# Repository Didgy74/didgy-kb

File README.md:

# didgy-kb
A catch-all repo for any keyboards I design.

These designs are all designed with [Ergogen](https://github.com/ergogen/ergogen).

# Mitten

This design has the following properties:
 - 30 keys
 - Split
 - Columnar stagger
 - Column splay on the outer columns
 - Wireless
 - Reversible PCB
 - (Very) Low profile (Choc Mini)
 - Choc spacing in Y direction
 - MX spacing in X direction
 - 1u keys for fingers
 - 1.5u keys for thumbs
 - Includes mountplate
 - Standard ProMicro support (Note that it's wireless only, so use a compatible MCU with Bluetooth connectivity)

In short, this design is heavily inspired by the [Ferris](https://github.com/pierrechevalier83/ferris) (or more specifically, the [Sweep](https://github.com/davidphilipbarr/Sweep)). This keyboard is very similar with a few key design differences:
 - Stagger adjusted for hands that have a short index finger
 - Outer columns are splayed
 - Removed one key from innermost column and outermost column.
 - Choc Mini support
 - Larger thumbkeys (1.5u)
 - Designed for wireless operation **only**
 - Includes mountplate

### Information

**Main PCB thickness:** 1.6mm

**Mount plate thickness:** 1.6mm

Mount plate is mostly for making the design sturdier and holding keys in place a bit better.

**Connector:** Molex PicoBlade 2-pin horizontal (Often mislabeled as Micro JST in stores)

**Key switches:** Kailh Choc Mini PG1232 (https://www.aliexpress.com/item/4000277394324.html)

Personal note: Try using 35g springs with linear (black) motion.

**MCU sockets:** Mill-Max Interconnect Machined Pin Socket. Pitch 2.54mm. Height above PCB: 7mm.
Part no. 801-XX-XXX-10-001000. You need at least 12 pins wide, any more can be broken off.

**Underside material:** Neoprene (need actual testing still)

**Keycaps:** MBK profile Choc (https://splitkb.com/collections/switches-and-keycaps/products/blank-mbk-choc-low-profile-keycaps)

**Power switch:** 7-pin micro SPDT

**MCU:** nice!nano

Xiao Seeed was considered for its smaller size, but since battery is mounted under the MCU, the battery would have to become too small anyways.

**MCU socket pins:** Mill-Max gold pins. Part no. 3320-0-00-15-00-00-03-0. (https://splitkb.com/collections/keyboard-parts/products/mill-max-low-profile-sockets?variant=32170972020813)

These could be thicker / longer, fit is not very good.

### Instructions

The MCU has to be mounted **face down** by default.

By default, all jumpers need to be shorted on the **opposite side** of where components are mounted.

### Future design work
I intend to keep iterating on this design over time, here are a few ideas I would like to eventually realize:
 - Add wired connectivity (but only if I, or a number of users request it)
 - Remove a key from the pinky column
 - **Possiby** try out a very low profile rotary encoder
 - Tighter vertical keyspacing (would require custom keycap work)
 - Choc Mini support
 - Add instructions for automatically routing the PCB

Other than that, I'll probably make adjustments to the stagger and key placement over time.

### Configuration 

While this is currently configured to fit my hands specifically, I am very much interested in creating a very parametric design. I try to keep the .yaml file commented enough to easily understand how to modify it. For instance, you could easily switch to using MX spacing by modifying the lines
```yaml
  keyspacingx: cx
  keyspacingy: cy
```
to
```yaml
  keyspacingx: u
  keyspacingy: u
```
and even switch to MX switch footprints by finding the YAML variable named `key_footprints`. Other configurable values currently include margin around key switches, rotation of the home thumbkey. I plan to add more of configuration in the future.

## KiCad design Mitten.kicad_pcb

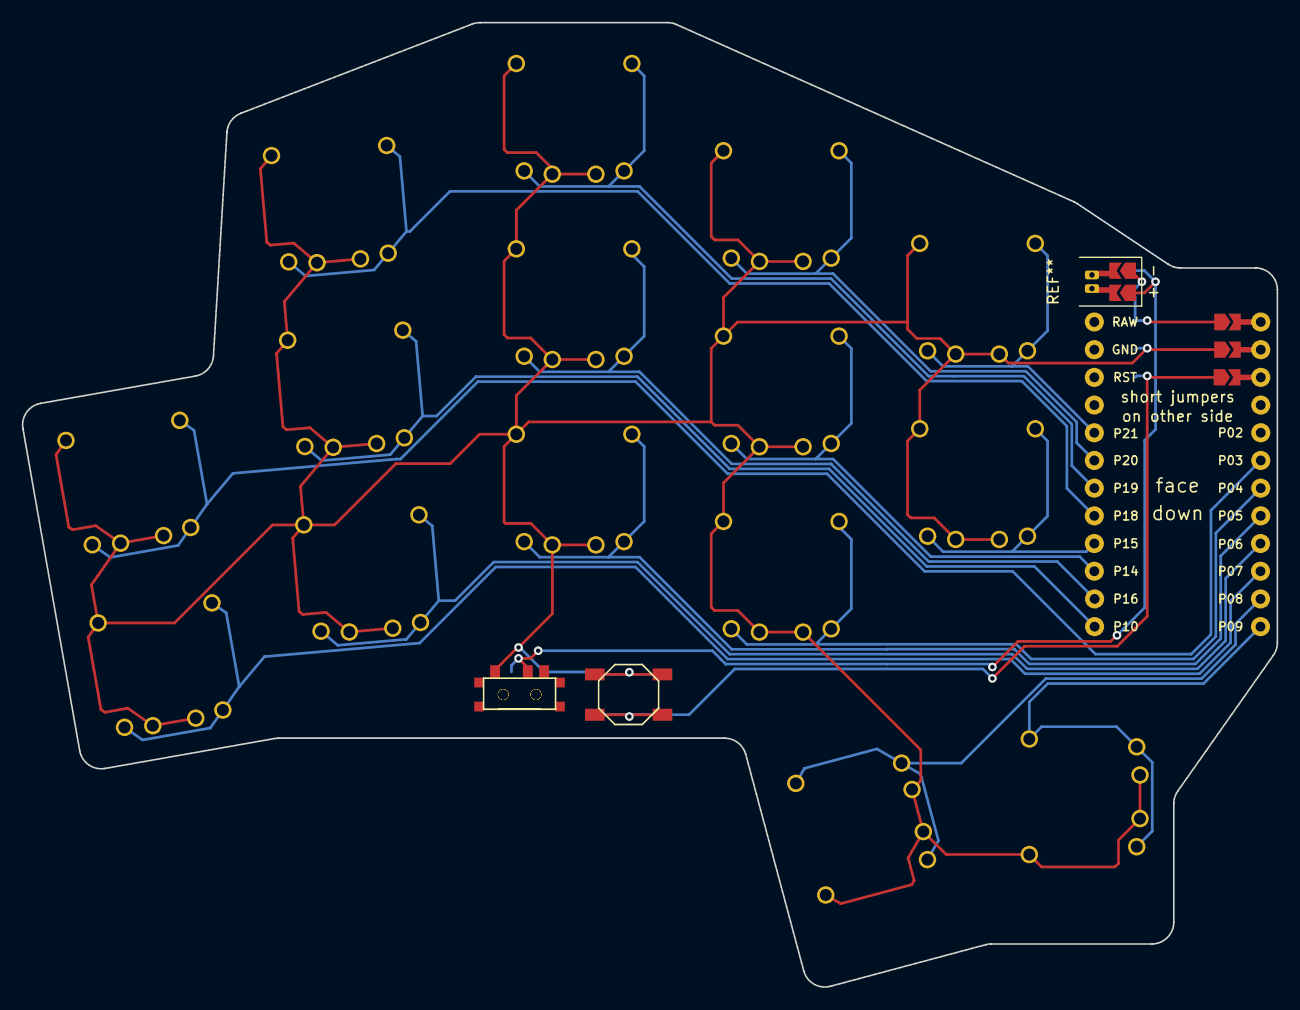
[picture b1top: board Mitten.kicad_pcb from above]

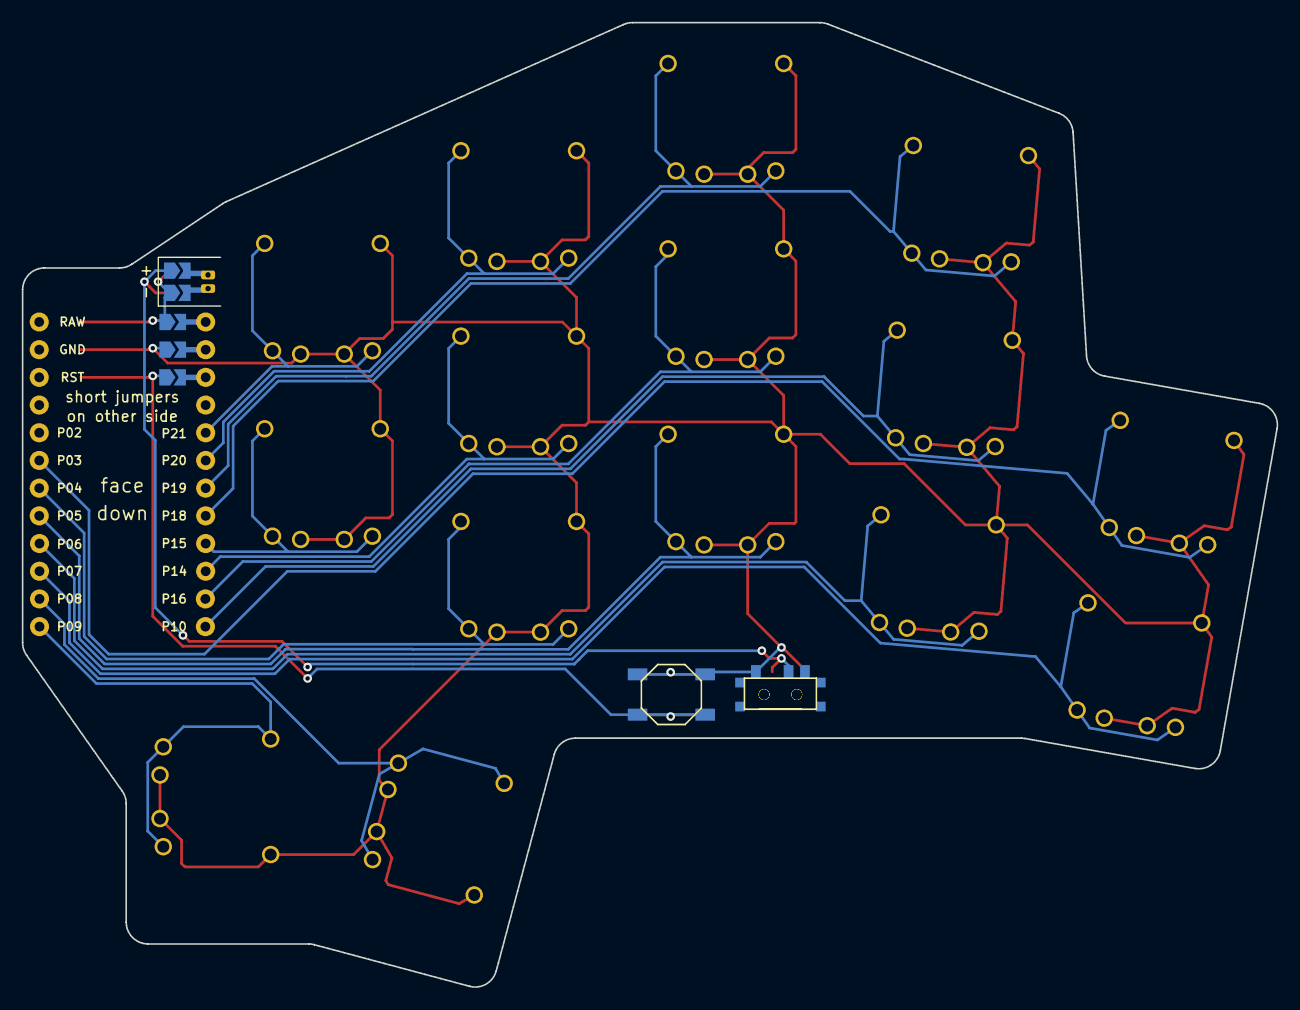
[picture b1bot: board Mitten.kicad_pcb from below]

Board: 2 copper layers, 115.1 x 88.5 mm, 20 parts (2 on the bottom side), 18 nets.

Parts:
B1, B1#2: SW_TACT_ALPS_SKQGABE010
MCU1: ProMicroReversible
S1, S2, S3, S4, S5, S6, S7, S8, S9, S10, S11, S12, S13, S14, S15: Choc Mini
T1, T1#2: SPDT_C128955

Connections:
Bminus: T1.2, T1#2.2
GND: B1.2, B1#2.2, MCU1.2, S1.2, S2.2, S3.2, S4.2, S5.2, S6.2, S7.2, S8.2, S9.2, S10.2, S11.2, S12.2, S13.2, S14.2, S15.2, T1.1, T1#2.1
RST: B1.1, B1#2.1, MCU1.3
home_default: MCU1.24, S14.1
index_bottom: MCU1.19, S9.1
index_home: MCU1.10, S10.1
index_topmost: MCU1.6, S11.1
innermost_bottom: MCU1.9, S12.1
innermost_topmost: MCU1.5, S13.1
middle_bottom: MCU1.20, S6.1
middle_home: MCU1.11, S7.1
middle_topmost: MCU1.7, S8.1
near_default: MCU1.23, S15.1
pinky_bottom: MCU1.22, S1.1
pinky_home: MCU1.18, S2.1
ring_bottom: MCU1.21, S3.1
ring_home: MCU1.12, S4.1
ring_topmost: MCU1.8, S5.1

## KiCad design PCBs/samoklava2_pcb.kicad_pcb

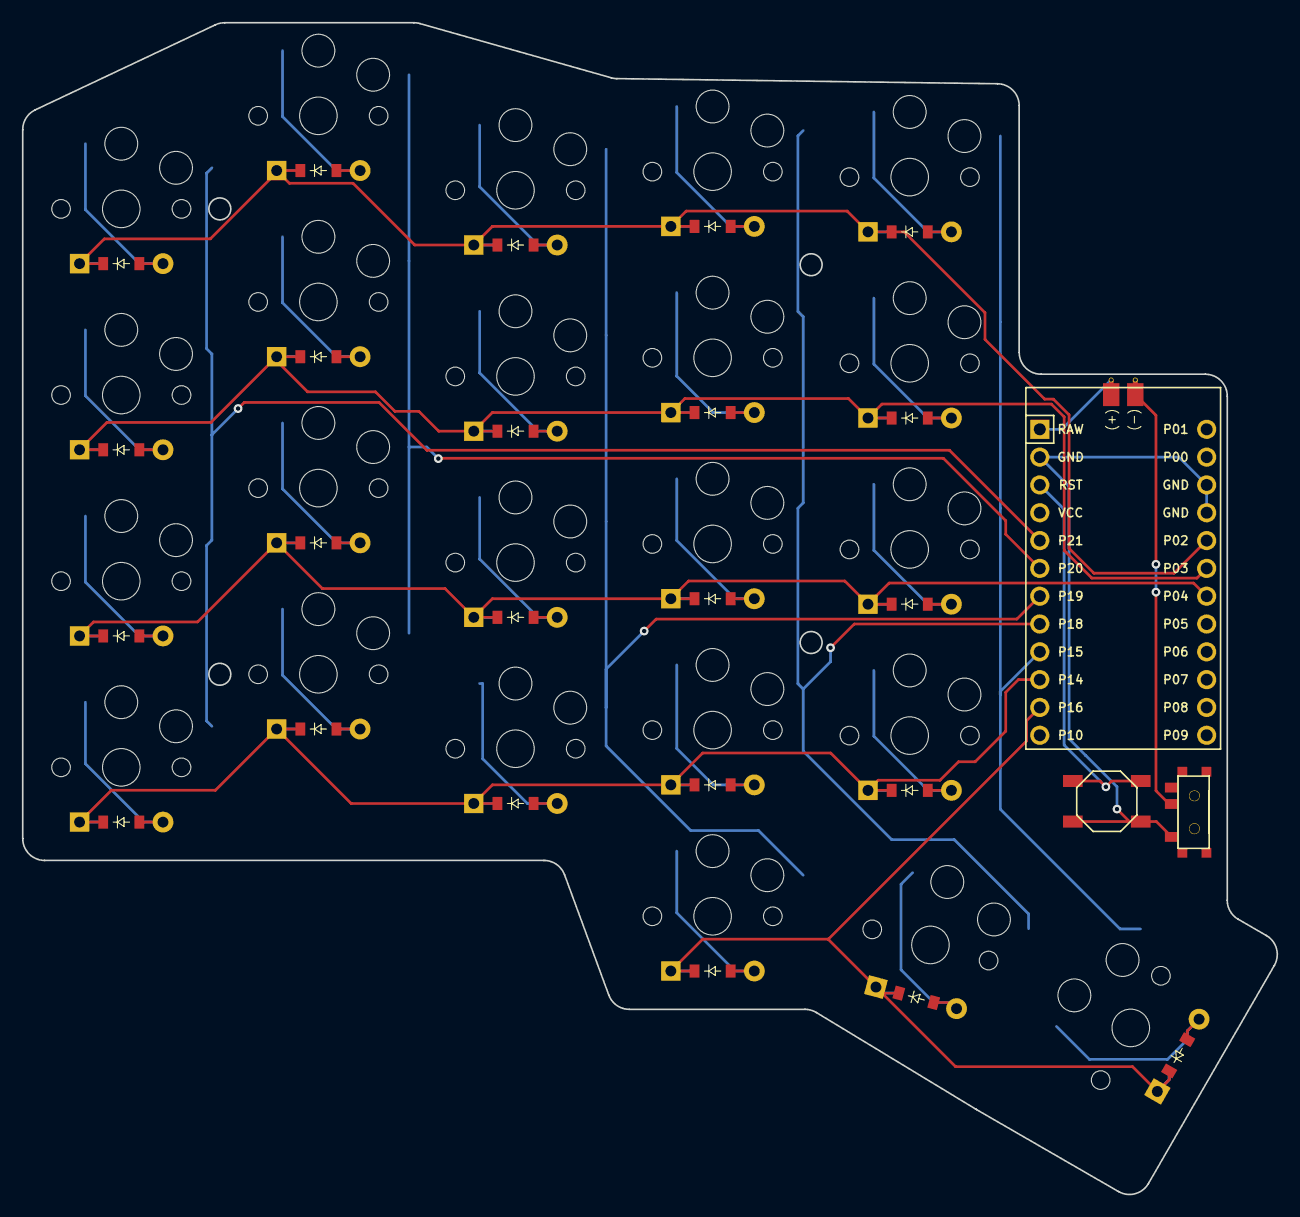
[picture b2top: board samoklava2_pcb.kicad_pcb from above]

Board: 2 copper layers, 114.6 x 107.0 mm, 50 parts (0 on the bottom side), 37 nets.

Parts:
B1: SW_TACT_ALPS_SKQGABE010
BT1: Battery_Cell; Battery_pads_reversible
D1, D2, D3, D4, D5, D6, D7, D8, D9, D10, D11, D12, D13, D14, D15, D16, D17, D18, D19, D20, D21, D22, D23: ComboDiode
MCU1: ProMicro
S1, S2, S3, S4, S5, S6, S7, S8, S9, S10, S11, S12, S13, S14, S15, S16, S17, S18, S19, S20, S21, S22, S23: PG1350
T1: SPDT_C128955

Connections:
Bminus: BT1.2, T1.2
GND: B1.2, MCU1.2, MCU1.15, MCU1.16, T1.1
P2: D4.1, D4.2, D8.1, D8.2, D12.1, D12.2, D16.1, D16.2, D20.1, D20.2, MCU1.17
P3: D3.1, D3.2, D7.1, D7.2, D11.1, D11.2, D15.1, D15.2, D19.1, D19.2, MCU1.18
P4: D2.1, D2.2, D6.1, D6.2, D10.1, D10.2, D14.1, D14.2, D18.1, D18.2, MCU1.19
P14: D1.1, D1.2, D5.1, D5.2, D9.1, D9.2, D13.1, D13.2, D17.1, D17.2, MCU1.10
P15: MCU1.9, S17.2, S18.2, S19.2, S20.2, S23.2
P16: D21.1, D21.2, D22.1, D22.2, D23.1, D23.2, MCU1.11
P18: MCU1.8, S13.2, S14.2, S15.2, S16.2, S22.2
P19: MCU1.7, S9.2, S10.2, S11.2, S12.2, S21.2
P20: MCU1.6, S5.2, S6.2, S7.2, S8.2
P21: MCU1.5, S1.2, S2.2, S3.2, S4.2
RAW: BT1.1, MCU1.1
RST: B1.1, MCU1.3
far_default: D23.1, D23.2, S23.1
home_default: D22.1, D22.2, S22.1
index_bottom: D13.1, D13.2, S13.1
index_home: D14.1, D14.2, S14.1
index_top: D15.1, D15.2, S15.1
index_topmost: D16.1, D16.2, S16.1
innermost_bottom: D17.1, D17.2, S17.1
innermost_home: D18.1, D18.2, S18.1
innermost_top: D19.1, D19.2, S19.1
innermost_topmost: D20.1, D20.2, S20.1
middle_bottom: D9.1, D9.2, S9.1
middle_home: D10.1, D10.2, S10.1
middle_top: D11.1, D11.2, S11.1
middle_topmost: D12.1, D12.2, S12.1
near_default: D21.1, D21.2, S21.1
pinky_bottom: D1.1, D1.2, S1.1
pinky_home: D2.1, D2.2, S2.1
pinky_top: D3.1, D3.2, S3.1
pinky_topmost: D4.1, D4.2, S4.1
ring_bottom: D5.1, D5.2, S5.1
ring_home: D6.1, D6.2, S6.1
ring_top: D7.1, D7.2, S7.1
ring_topmost: D8.1, D8.2, S8.1

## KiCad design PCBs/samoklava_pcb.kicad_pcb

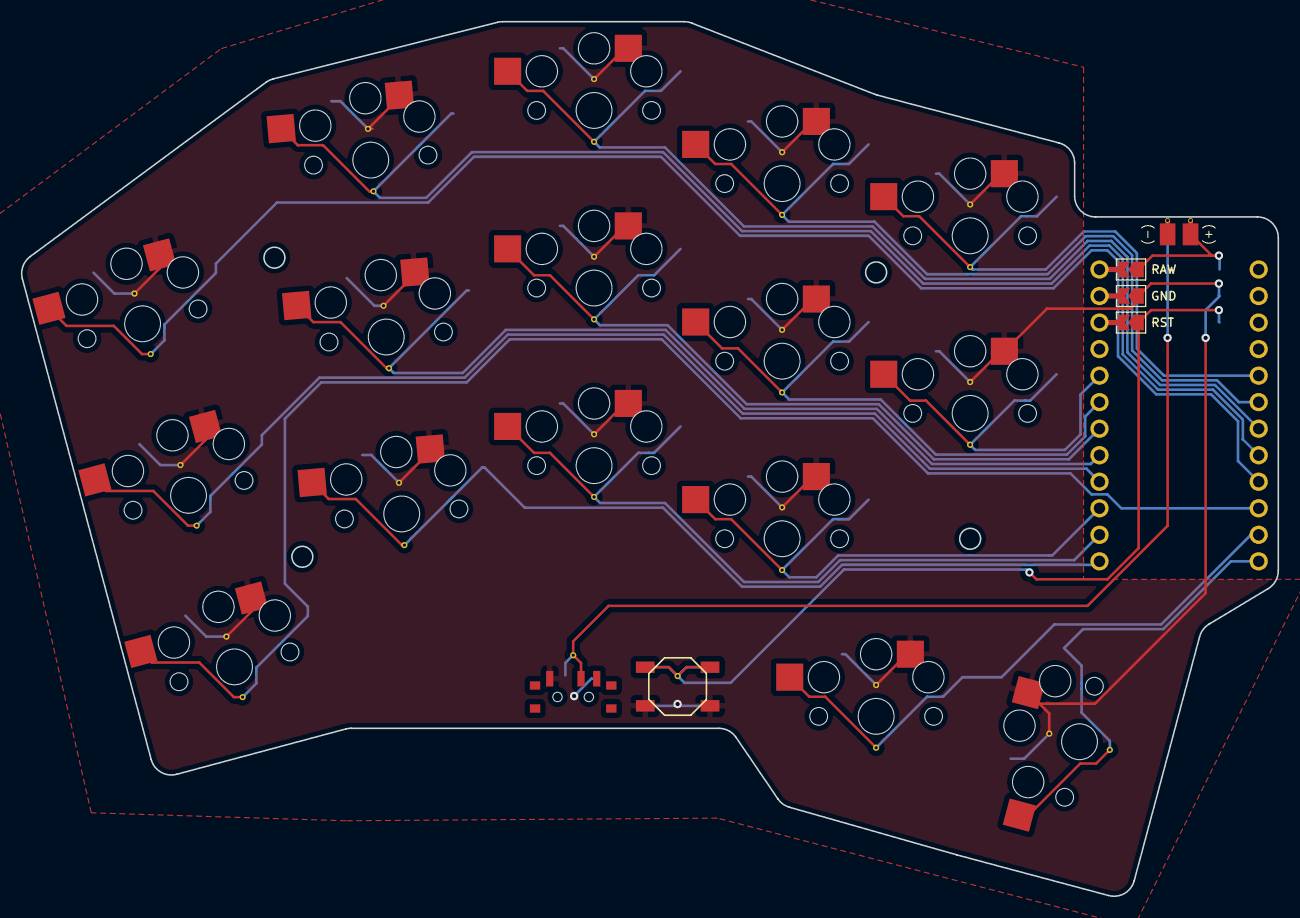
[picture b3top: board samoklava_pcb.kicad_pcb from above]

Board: 2 copper layers, 120.3 x 83.7 mm, 21 parts (1 on the bottom side), 20 nets.

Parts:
B1, B2: SW_TACT_ALPS_SKQGABE010
BT1: Battery_Cell; Battery_pads_reversible
MCU1: Val**; ProMicroSimpleJumper
S1, S2, S3, S4, S5, S6, S7, S8, S9, S10, S11, S12, S13, S14, S15, S16: PG1350
T1: Power_reversible

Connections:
Bminus: BT1.2, T1.2
GND: B1.2, B2.2, MCU1.2, S1.1, S2.1, S3.1, S4.1, S5.1, S6.1, S7.1, S8.1, S9.1, S10.1, S11.1, S12.1, S13.1, S14.1, S15.1, S16.1, T1.1
P2: MCU1.17, S14.2
P3: MCU1.18, S12.2
P4: MCU1.19, S9.2
P5: MCU1.20, S6.2
P6: MCU1.21, S3.2
P7: MCU1.22, S1.2
P8: MCU1.23, S15.2
P9: MCU1.24, S16.2
P10: MCU1.12, S4.2
P14: MCU1.10, S10.2
P15: MCU1.9, S2.2
P16: MCU1.11, S7.2
P18: MCU1.8, S5.2
P19: MCU1.7, S8.2
P20: MCU1.6, S11.2
P21: MCU1.5, S13.2
RAW: BT1.1, MCU1.1
RST: B1.1, B2.1, MCU1.3

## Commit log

2022-02-28 Updated the README
2022-02-28 Fixed typo in README.md
